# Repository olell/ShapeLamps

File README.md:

# ShapeLamps

## Software Features
- [x] Easy AP-Based wifi configuration
- [x] OTA Firmware & Filesystem updates
- [x] Easy to use webinterface
- [x] Fancy Animations
- [x] Sleeptimer
- [x] Waketimer
- [x] Wake alarm sounds
- [x] Theoretically compatible with other hardware

## Renderings

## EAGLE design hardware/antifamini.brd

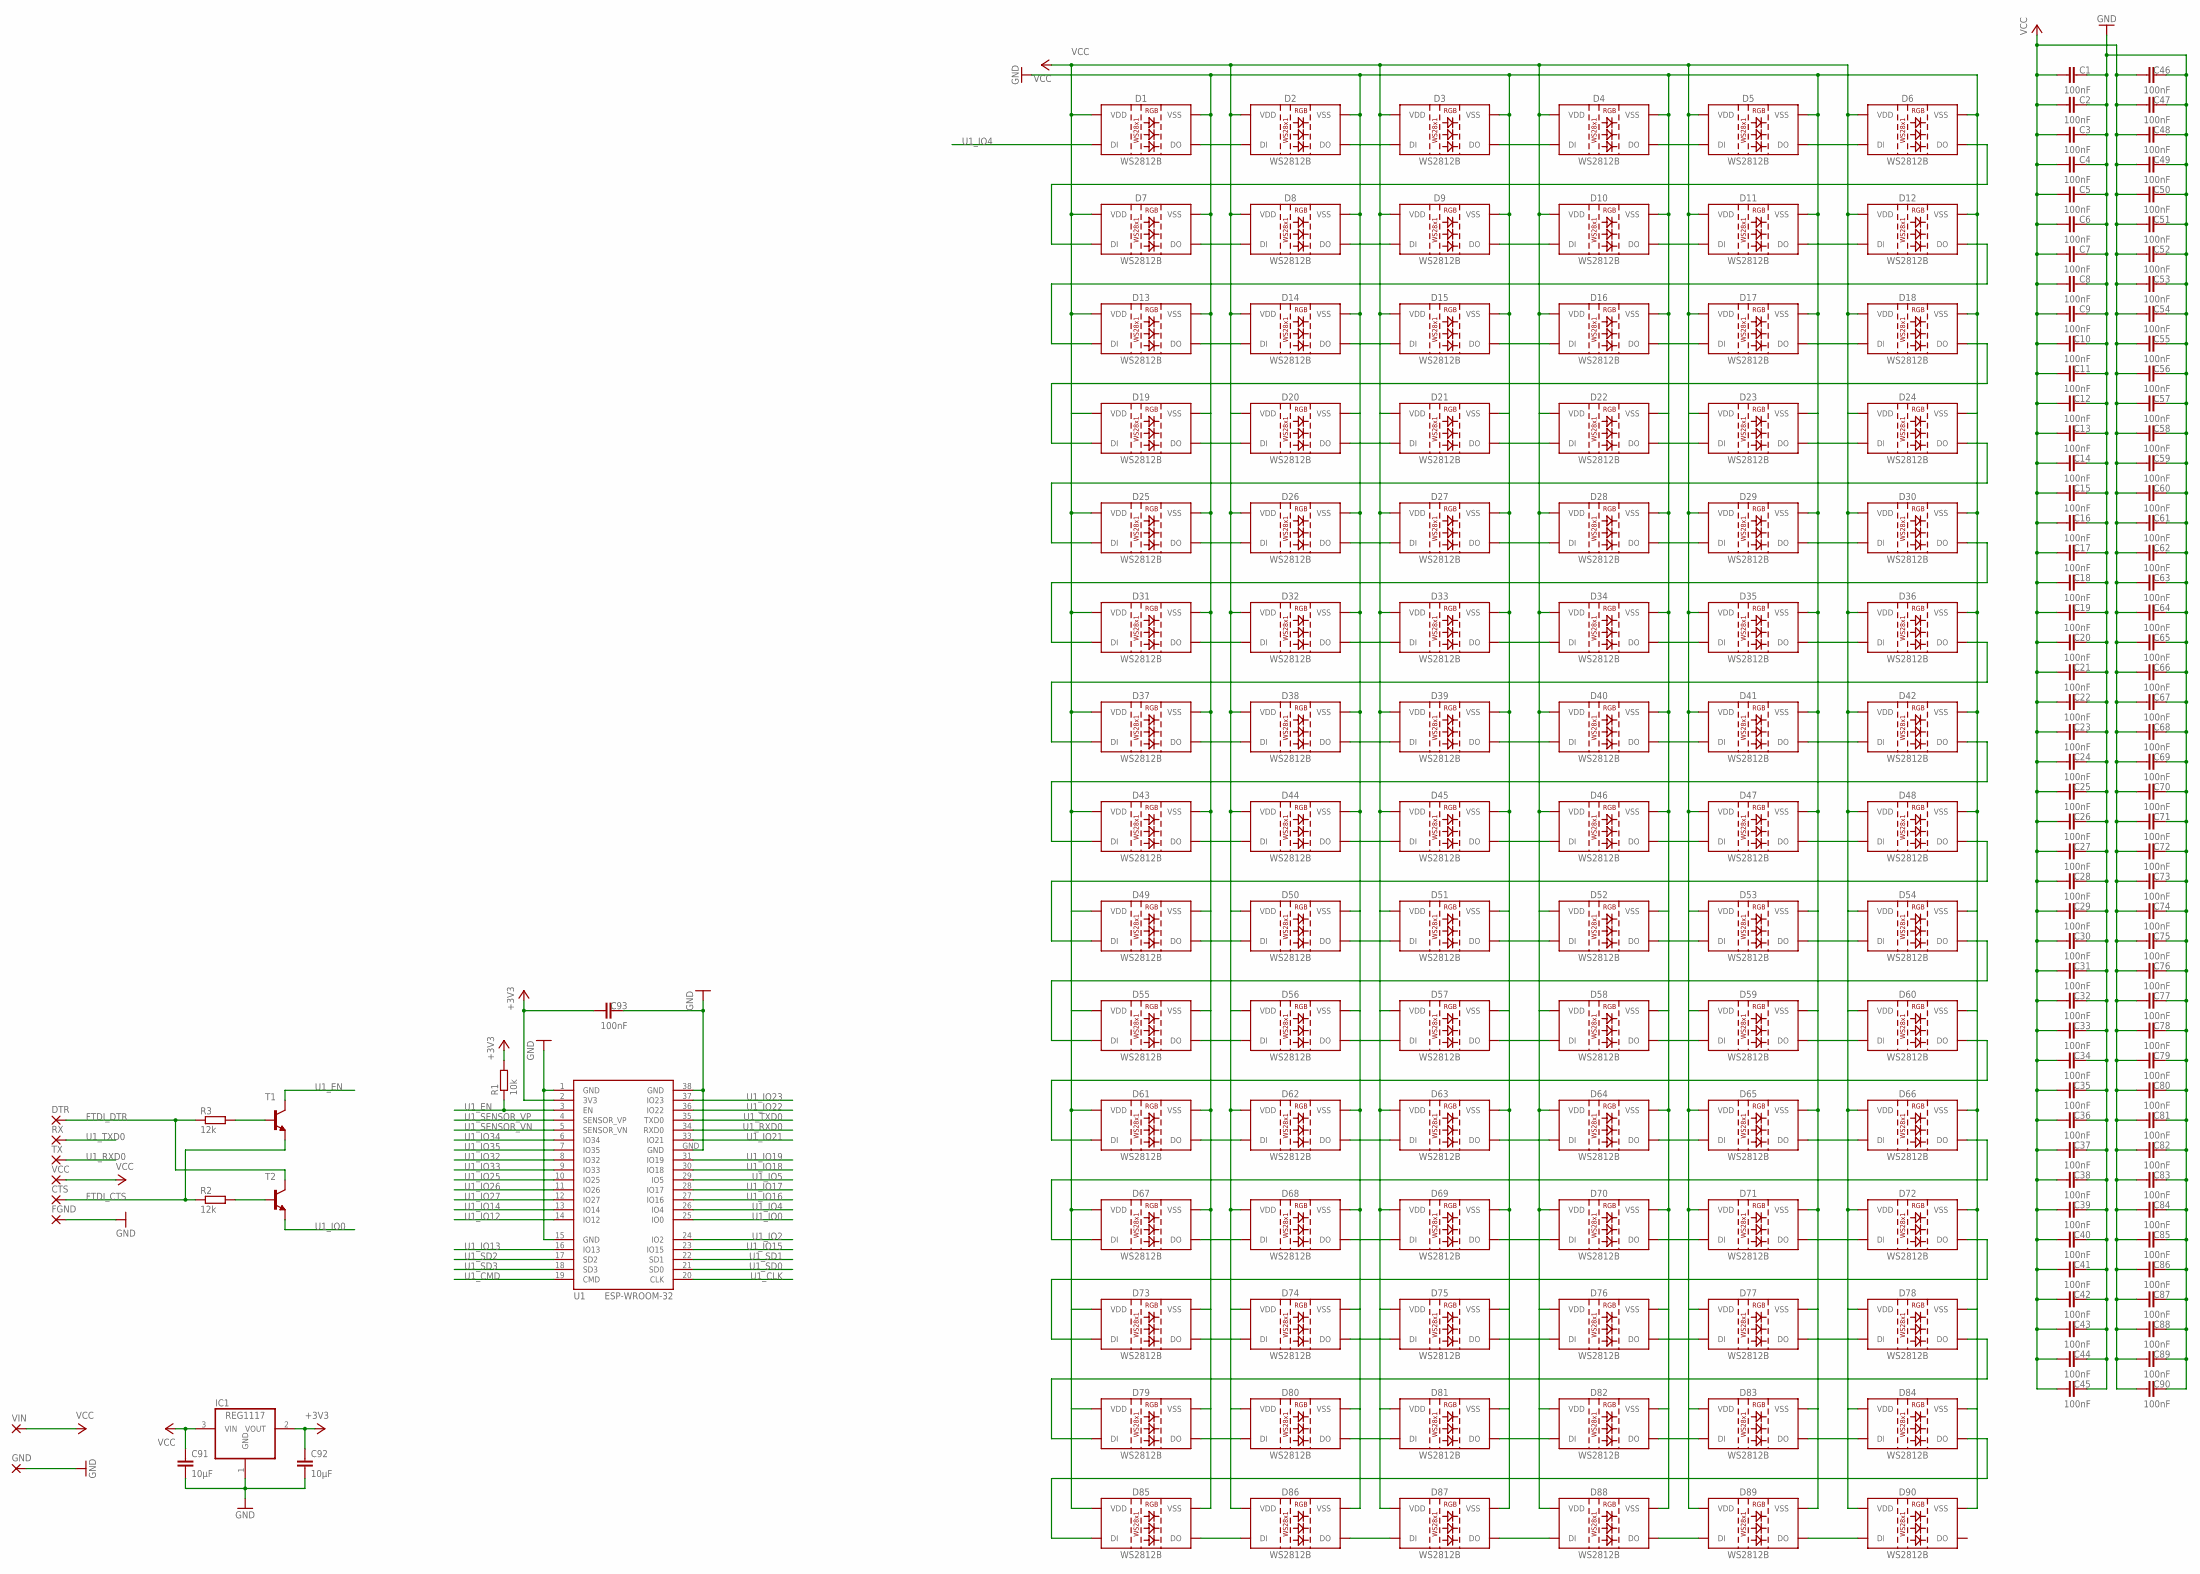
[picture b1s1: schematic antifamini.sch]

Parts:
C1, C2, C3, C4, C5, C6, C7, C8, C9, C10, C11, C12, C13, C14, C15, C16, C17, C18, C19, C20, C21, C22, C23, C24, C25, C26, C27, C28, C29, C30, C31, C32, C33, C34, C35, C36, C37, C38, C39, C40, C41, C42, C43, C44, C45, C46, C47, C48, C49, C50, C51, C52, C53, C54, C55, C56, C57, C58, C59, C60, C61, C62, C63, C64, C65, C66, C67, C68, C69, C70, C71, C72, C73, C74, C75, C76, C77, C78, C79, C80, C81, C82, C83, C84, C85, C86, C87, C88, C89, C90, C93: 100nF; C0603
C91, C92: 10µF; C1206K
CTS: SMD2; SMD1,27-2,54
D1, D2, D3, D4, D5, D6, D7, D8, D9, D10, D11, D12, D13, D14, D15, D16, D17, D18, D19, D20, D21, D22, D23, D24, D25, D26, D27, D28, D29, D30, D31, D32, D33, D34, D35, D36, D37, D38, D39, D40, D41, D42, D43, D44, D45, D46, D47, D48, D49, D50, D51, D52, D53, D54, D55, D56, D57, D58, D59, D60, D61, D62, D63, D64, D65, D66, D67, D68, D69, D70, D71, D72, D73, D74, D75, D76, D77, D78, D79, D80, D81, D82, D83, D84, D85, D86, D87, D88, D89, D90: WS2812B
DTR: SMD2; SMD1,27-2,54
FGND: SMD2; SMD1,27-2,54
GND: SMD5; SMD2,54-5,08
IC1: REG1117; SOT223
R1: 10k; R0603
R2, R3: 12k; R0603
RX: SMD2; SMD1,27-2,54
T1, T2: BC818-40-NPN-SOT23-BEC; SOT23-BEC
TX: SMD2; SMD1,27-2,54
U1: ESP-WROOM-32
VCC: SMD2; SMD1,27-2,54
VIN: SMD5; SMD2,54-5,08

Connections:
+3V3: C92.1, C93.2, IC1.2 (VOUT), R1.2, U1.2 (3V3)
FTDI_CTS: CTS.1, R2.1, T1.E
FTDI_DTR: DTR.1, R3.1, T2.C
GND: C1.1, C2.1, C3.1, C4.1, C5.1, C6.1, C7.1, C8.1, C9.1, C10.1, C11.1, C12.1, C13.1, C14.1, C15.1, C16.1, C17.1, C18.1, C19.1, C20.1, C21.1, C22.1, C23.1, C24.1, C25.1, C26.1, C27.1, C28.1, C29.1, C30.1, C31.1, C32.1, C33.1, C34.1, C35.1, C36.1, C37.1, C38.1, C39.1, C40.1, C41.1, C42.1, C43.1, C44.1, C45.1, C46.1, C47.1, C48.1, C49.1, C50.1, C51.1, C52.1, C53.1, C54.1, C55.1, C56.1, C57.1, C58.1, C59.1, C60.1, C61.1, C62.1, C63.1, C64.1, C65.1, C66.1, C67.1, C68.1, C69.1, C70.1, C71.1, C72.1, C73.1, C74.1, C75.1, C76.1, C77.1, C78.1, C79.1, C80.1, C81.1, C82.1, C83.1, C84.1, C85.1, C86.1, C87.1, C88.1, C89.1, C90.1, C91.2, C92.2, C93.1, D1.3 (VSS), D2.3 (VSS), D3.3 (VSS), D4.3 (VSS), D5.3 (VSS), D6.3 (VSS), D7.3 (VSS), D8.3 (VSS), D9.3 (VSS), D10.3 (VSS), D11.3 (VSS), D12.3 (VSS), D13.3 (VSS), D14.3 (VSS), D15.3 (VSS), D16.3 (VSS), D17.3 (VSS), D18.3 (VSS), D19.3 (VSS), D20.3 (VSS), D21.3 (VSS), D22.3 (VSS), D23.3 (VSS), D24.3 (VSS), D25.3 (VSS), D26.3 (VSS), D27.3 (VSS), D28.3 (VSS), D29.3 (VSS), D30.3 (VSS), D31.3 (VSS), D32.3 (VSS), D33.3 (VSS), D34.3 (VSS), D35.3 (VSS), D36.3 (VSS), D37.3 (VSS), D38.3 (VSS), D39.3 (VSS), D40.3 (VSS), D41.3 (VSS), D42.3 (VSS), D43.3 (VSS), D44.3 (VSS), D45.3 (VSS), D46.3 (VSS), D47.3 (VSS), D48.3 (VSS), D49.3 (VSS), D50.3 (VSS), D51.3 (VSS), D52.3 (VSS), D53.3 (VSS), D54.3 (VSS), D55.3 (VSS), D56.3 (VSS), D57.3 (VSS), D58.3 (VSS), D59.3 (VSS), D60.3 (VSS), D61.3 (VSS), D62.3 (VSS), D63.3 (VSS), D64.3 (VSS), D65.3 (VSS), D66.3 (VSS), D67.3 (VSS), D68.3 (VSS), D69.3 (VSS), D70.3 (VSS), D71.3 (VSS), D72.3 (VSS), D73.3 (VSS), D74.3 (VSS), D75.3 (VSS), D76.3 (VSS), D77.3 (VSS), D78.3 (VSS), D79.3 (VSS), D80.3 (VSS), D81.3 (VSS), D82.3 (VSS), D83.3 (VSS), D84.3 (VSS), D85.3 (VSS), D86.3 (VSS), D87.3 (VSS), D88.3 (VSS), D89.3 (VSS), D90.3 (VSS), FGND.1, GND.1, IC1.1 (GND), U1.1 (GND), U1.15 (GND), U1.38 (GND), U1.GND
unnamed: D1.2 (DO), D2.4 (DI)
unnamed: D2.2 (DO), D3.4 (DI)
unnamed: D3.2 (DO), D4.4 (DI)
unnamed: D4.2 (DO), D5.4 (DI)
unnamed: D5.2 (DO), D6.4 (DI)
unnamed: D6.2 (DO), D7.4 (DI)
unnamed: D7.2 (DO), D8.4 (DI)
unnamed: D8.2 (DO), D9.4 (DI)
unnamed: D9.2 (DO), D10.4 (DI)
unnamed: D10.2 (DO), D11.4 (DI)
unnamed: D11.2 (DO), D12.4 (DI)
unnamed: D12.2 (DO), D13.4 (DI)
unnamed: D13.2 (DO), D14.4 (DI)
unnamed: D14.2 (DO), D15.4 (DI)
unnamed: D15.2 (DO), D16.4 (DI)
unnamed: D16.2 (DO), D17.4 (DI)
unnamed: D17.2 (DO), D18.4 (DI)
unnamed: D18.2 (DO), D19.4 (DI)
unnamed: D19.2 (DO), D20.4 (DI)
unnamed: D20.2 (DO), D21.4 (DI)
unnamed: D21.2 (DO), D22.4 (DI)
unnamed: D22.2 (DO), D23.4 (DI)
unnamed: D23.2 (DO), D24.4 (DI)
unnamed: D24.2 (DO), D25.4 (DI)
unnamed: D25.2 (DO), D26.4 (DI)
unnamed: D26.2 (DO), D27.4 (DI)
unnamed: D27.2 (DO), D28.4 (DI)
unnamed: D28.2 (DO), D29.4 (DI)
unnamed: D29.2 (DO), D30.4 (DI)
unnamed: D31.2 (DO), D32.4 (DI)
unnamed: D32.2 (DO), D33.4 (DI)
unnamed: D33.2 (DO), D34.4 (DI)
unnamed: D34.2 (DO), D35.4 (DI)
unnamed: D35.2 (DO), D36.4 (DI)
unnamed: D36.2 (DO), D37.4 (DI)
unnamed: D37.2 (DO), D38.4 (DI)
unnamed: D38.2 (DO), D39.4 (DI)
unnamed: D39.2 (DO), D40.4 (DI)
unnamed: D40.2 (DO), D41.4 (DI)
unnamed: D41.2 (DO), D42.4 (DI)
unnamed: D42.2 (DO), D43.4 (DI)
unnamed: D43.2 (DO), D44.4 (DI)
unnamed: D44.2 (DO), D45.4 (DI)
unnamed: D45.2 (DO), D46.4 (DI)
unnamed: D46.2 (DO), D47.4 (DI)
unnamed: D47.2 (DO), D48.4 (DI)
unnamed: D48.2 (DO), D49.4 (DI)
unnamed: D49.2 (DO), D50.4 (DI)
unnamed: D50.2 (DO), D51.4 (DI)
unnamed: D51.2 (DO), D52.4 (DI)
unnamed: D52.2 (DO), D53.4 (DI)
unnamed: D53.2 (DO), D54.4 (DI)
unnamed: D54.2 (DO), D55.4 (DI)
unnamed: D55.2 (DO), D56.4 (DI)
unnamed: D56.2 (DO), D57.4 (DI)
unnamed: D57.2 (DO), D58.4 (DI)
unnamed: D58.2 (DO), D59.4 (DI)
unnamed: D59.2 (DO), D60.4 (DI)
unnamed: D30.2 (DO), D31.4 (DI)
unnamed: D60.2 (DO), D61.4 (DI)
unnamed: D61.2 (DO), D62.4 (DI)
unnamed: D62.2 (DO), D63.4 (DI)
unnamed: D63.2 (DO), D64.4 (DI)
unnamed: D64.2 (DO), D65.4 (DI)
unnamed: D65.2 (DO), D66.4 (DI)
unnamed: D66.2 (DO), D67.4 (DI)
unnamed: D67.2 (DO), D68.4 (DI)
unnamed: D68.2 (DO), D69.4 (DI)
unnamed: D69.2 (DO), D70.4 (DI)
unnamed: D70.2 (DO), D71.4 (DI)
unnamed: D71.2 (DO), D72.4 (DI)
unnamed: D72.2 (DO), D73.4 (DI)
unnamed: D73.2 (DO), D74.4 (DI)
unnamed: D74.2 (DO), D75.4 (DI)
unnamed: D75.2 (DO), D76.4 (DI)
unnamed: D76.2 (DO), D77.4 (DI)
unnamed: D77.2 (DO), D78.4 (DI)
unnamed: D78.2 (DO), D79.4 (DI)
unnamed: D79.2 (DO), D80.4 (DI)
unnamed: D80.2 (DO), D81.4 (DI)
unnamed: D81.2 (DO), D82.4 (DI)
unnamed: D82.2 (DO), D83.4 (DI)
unnamed: D83.2 (DO), D84.4 (DI)
unnamed: D84.2 (DO), D85.4 (DI)
unnamed: D85.2 (DO), D86.4 (DI)
unnamed: D86.2 (DO), D87.4 (DI)
unnamed: D87.2 (DO), D88.4 (DI)
unnamed: D88.2 (DO), D89.4 (DI)
unnamed: D89.2 (DO), D90.4 (DI)
unnamed: R3.2, T1.B
unnamed: R2.2, T2.B
U1_CLK: U1.20 (CLK)
U1_CMD: U1.19 (CMD)
U1_EN: R1.1, T1.C, U1.3 (EN)
U1_IO0: T2.E, U1.25 (IO0)
U1_IO2: U1.24 (IO2)
U1_IO4: D1.4 (DI), U1.26 (IO4)
U1_IO5: U1.29 (IO5)
U1_IO12: U1.14 (IO12)
U1_IO13: U1.16 (IO13)
U1_IO14: U1.13 (IO14)
U1_IO15: U1.23 (IO15)
U1_IO16: U1.27 (IO16)
U1_IO17: U1.28 (IO17)
U1_IO18: U1.30 (IO18)
U1_IO19: U1.31 (IO19)
U1_IO21: U1.33 (IO21)
U1_IO22: U1.36 (IO22)
U1_IO23: U1.37 (IO23)
U1_IO25: U1.10 (IO25)
U1_IO26: U1.11 (IO26)
U1_IO27: U1.12 (IO27)
U1_IO32: U1.8 (IO32)
U1_IO33: U1.9 (IO33)
U1_IO34: U1.6 (IO34)
U1_IO35: U1.7 (IO35)
U1_RXD0: TX.1, U1.34 (RXD0)
U1_SD0: U1.21 (SD0)
U1_SD1: U1.22 (SD1)
U1_SD2: U1.17 (SD2)
U1_SD3: U1.18 (SD3)
U1_SENSOR_VN: U1.5 (SENSOR_VN)
U1_SENSOR_VP: U1.4 (SENSOR_VP)
U1_TXD0: RX.1, U1.35 (TXD0)
VCC: C1.2, C2.2, C3.2, C4.2, C5.2, C6.2, C7.2, C8.2, C9.2, C10.2, C11.2, C12.2, C13.2, C14.2, C15.2, C16.2, C17.2, C18.2, C19.2, C20.2, C21.2, C22.2, C23.2, C24.2, C25.2, C26.2, C27.2, C28.2, C29.2, C30.2, C31.2, C32.2, C33.2, C34.2, C35.2, C36.2, C37.2, C38.2, C39.2, C40.2, C41.2, C42.2, C43.2, C44.2, C45.2, C46.2, C47.2, C48.2, C49.2, C50.2, C51.2, C52.2, C53.2, C54.2, C55.2, C56.2, C57.2, C58.2, C59.2, C60.2, C61.2, C62.2, C63.2, C64.2, C65.2, C66.2, C67.2, C68.2, C69.2, C70.2, C71.2, C72.2, C73.2, C74.2, C75.2, C76.2, C77.2, C78.2, C79.2, C80.2, C81.2, C82.2, C83.2, C84.2, C85.2, C86.2, C87.2, C88.2, C89.2, C90.2, C91.1, D1.1 (VDD), D2.1 (VDD), D3.1 (VDD), D4.1 (VDD), D5.1 (VDD), D6.1 (VDD), D7.1 (VDD), D8.1 (VDD), D9.1 (VDD), D10.1 (VDD), D11.1 (VDD), D12.1 (VDD), D13.1 (VDD), D14.1 (VDD), D15.1 (VDD), D16.1 (VDD), D17.1 (VDD), D18.1 (VDD), D19.1 (VDD), D20.1 (VDD), D21.1 (VDD), D22.1 (VDD), D23.1 (VDD), D24.1 (VDD), D25.1 (VDD), D26.1 (VDD), D27.1 (VDD), D28.1 (VDD), D29.1 (VDD), D30.1 (VDD), D31.1 (VDD), D32.1 (VDD), D33.1 (VDD), D34.1 (VDD), D35.1 (VDD), D36.1 (VDD), D37.1 (VDD), D38.1 (VDD), D39.1 (VDD), D40.1 (VDD), D41.1 (VDD), D42.1 (VDD), D43.1 (VDD), D44.1 (VDD), D45.1 (VDD), D46.1 (VDD), D47.1 (VDD), D48.1 (VDD), D49.1 (VDD), D50.1 (VDD), D51.1 (VDD), D52.1 (VDD), D53.1 (VDD), D54.1 (VDD), D55.1 (VDD), D56.1 (VDD), D57.1 (VDD), D58.1 (VDD), D59.1 (VDD), D60.1 (VDD), D61.1 (VDD), D62.1 (VDD), D63.1 (VDD), D64.1 (VDD), D65.1 (VDD), D66.1 (VDD), D67.1 (VDD), D68.1 (VDD), D69.1 (VDD), D70.1 (VDD), D71.1 (VDD), D72.1 (VDD), D73.1 (VDD), D74.1 (VDD), D75.1 (VDD), D76.1 (VDD), D77.1 (VDD), D78.1 (VDD), D79.1 (VDD), D80.1 (VDD), D81.1 (VDD), D82.1 (VDD), D83.1 (VDD), D84.1 (VDD), D85.1 (VDD), D86.1 (VDD), D87.1 (VDD), D88.1 (VDD), D89.1 (VDD), D90.1 (VDD), IC1.3 (VIN), VCC.1, VIN.1

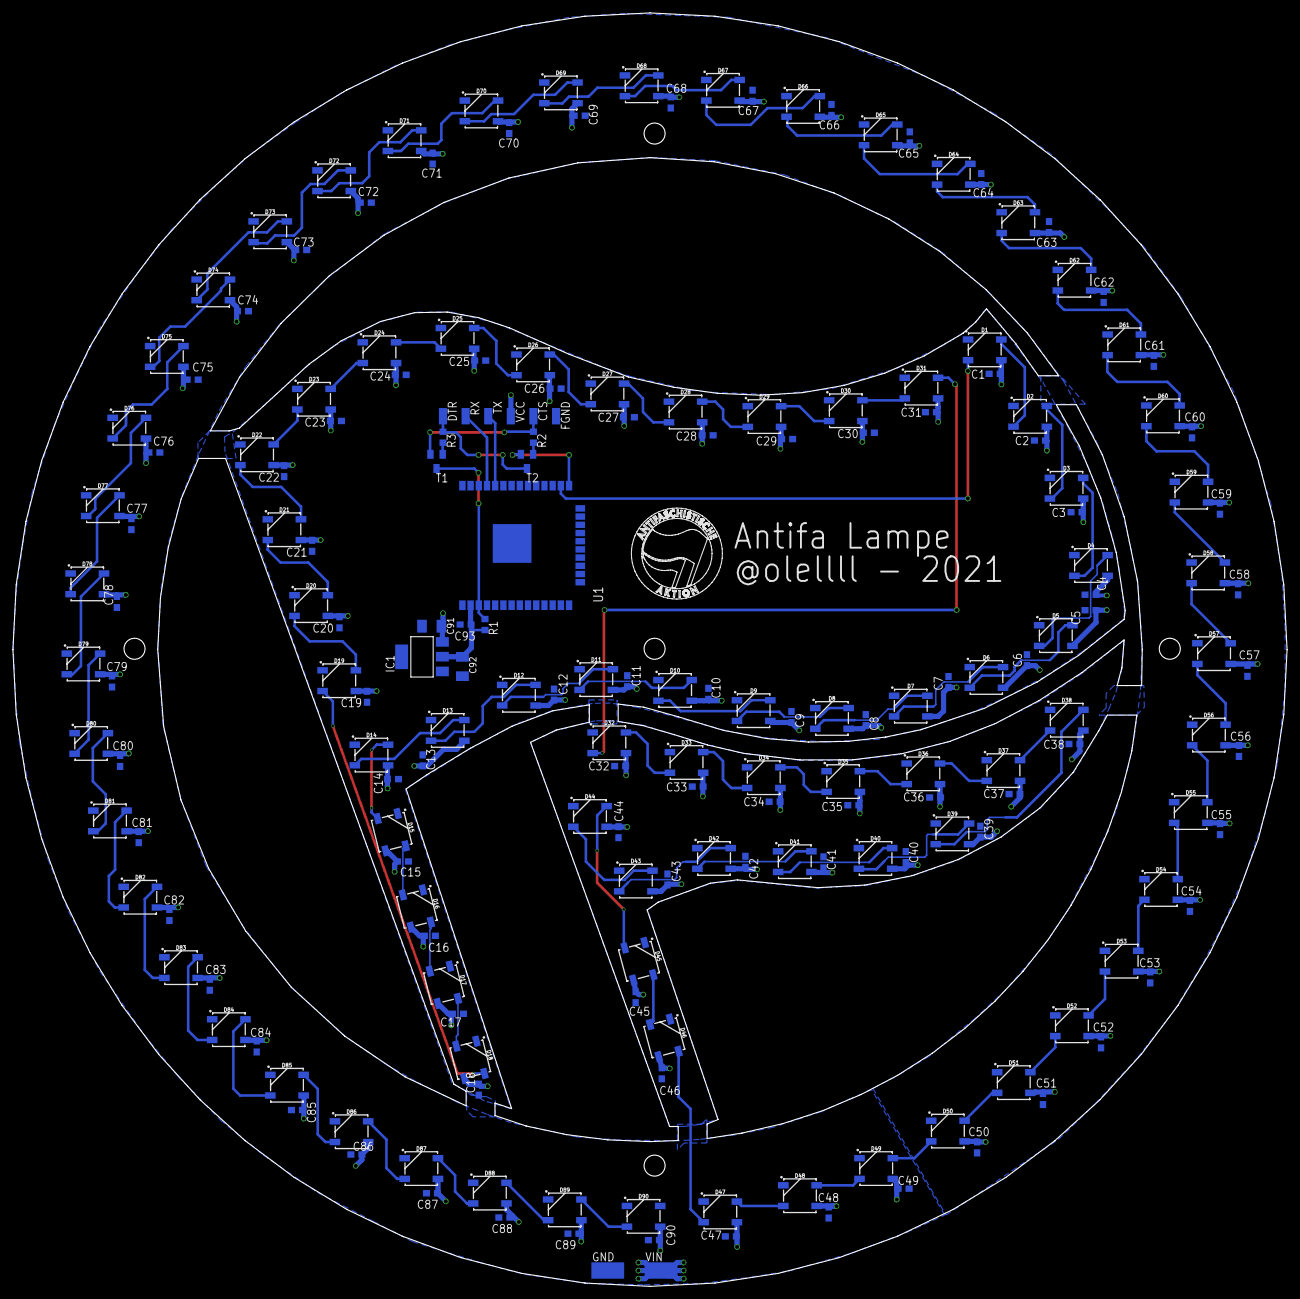
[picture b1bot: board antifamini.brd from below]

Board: 2 copper layers, 197.2 x 197.1 mm, 198 parts (198 on the bottom side), 101 nets.

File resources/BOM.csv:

NAME,VALUE,PART,AMOUNT
,,,
IC1,,NCP 1117 ST33T3G,1
U1,,ESP-WROOM-32,1
,,,
R1,10k,Resistor 0603,1
"R2,R3",12k,Resistor 0603,2
,,,
"T1,T2",,BC 818-40 SMD,2
D1-D90,,LED5050 WS2812B,90
,,,
"C91,C92",10µF,"SMD Tantal (3,2x1,6mm)",2
"C1-C90, C93",100nF,Capacitor 0603,91
,,,
PCB,,,

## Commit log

2021-01-03 Added hardware files
2021-01-03 Added renderings
2021-01-03 Added renderings to README
2021-01-03 Added software
2021-01-12 Started rewriting software with pio
2021-01-12 Added BOM
2021-01-12 Implemented wifi behavior config
2021-01-13 Added AP ssid/psk to config
2021-01-13 Added wifi to log_config dump
2021-01-13 Started implementation of wifi driver
2021-01-13 Implemented r/w of wifi credentials to spiffs
2021-01-13 Some explanation added
2021-01-17 Started implementation of webserver
2021-01-18 Changed from slim to normal jquery version
2021-01-25 Muuuch stuffs done
2021-01-25 Implemented settings page
2021-01-25 Added device silhouette
2021-01-25 removed -prototype from hostname
2021-01-26 New logo
2021-01-26 Little success color display fix
2021-01-26 Missing slider in chrome fixed
2021-01-26 Changed HSV to RGB behavior
2021-01-26 renamed driver to led_driver
2021-01-26 Added simple sdl2 simulator (fire anim hardcode)
2021-01-26 Add: clock animation
2021-01-26 Add: Random fade animation to webinterface
2021-01-28 Add: Plasma Animation
2021-01-29 Updated meta headers
2021-01-29 Fixed brightness bug in firmware updater
2021-01-29 Added sleep timer
2021-01-29 Added software features to readme
2021-01-30 Implemented first version of external animations
2021-01-31 Add: Some brightness correction
2021-01-31 correction array generator added
2021-01-31 Implemented wake timer in backend
2021-02-15 Implemented wake timer
2021-02-15 Added wake timer feature
2021-02-16 little fix in clock animation
2021-02-16 alarm tone + factory reset :)

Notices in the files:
parts and their libraries:
SparkFun-LED: Licensing: Creative Commons ShareAlike 4.0 International - https://creativecommons.org/licenses/by-sa/4.0
esp32: Creative Commons Attribution-ShareAlike 4.0 International
